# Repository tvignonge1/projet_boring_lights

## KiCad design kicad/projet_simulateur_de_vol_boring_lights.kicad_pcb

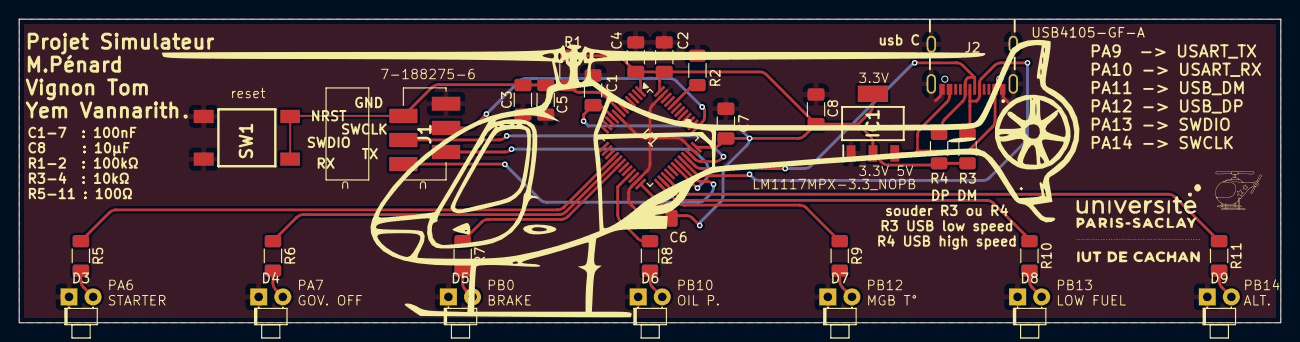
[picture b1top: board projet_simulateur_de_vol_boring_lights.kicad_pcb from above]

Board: 2 copper layers, 133.0 x 32.0 mm, 31 parts (0 on the bottom side), 25 nets.

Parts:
C1, C2, C3, C4, C5, C6, C7: 100n; C_1206_3216Metric_Pad1.33x1.80mm_HandSolder
C8: 10µ; C_1206_3216Metric_Pad1.33x1.80mm_HandSolder
D3: LED_starter; LED_D1.8mm_W1.8mm_H2.4mm_Horizontal_O1.27mm_Z1.6mm
D4: LED_gov.off; LED_D1.8mm_W1.8mm_H2.4mm_Horizontal_O1.27mm_Z1.6mm
D5: LED_brake; LED_D1.8mm_W1.8mm_H2.4mm_Horizontal_O1.27mm_Z1.6mm
D6: LED_oilP; LED_D1.8mm_W1.8mm_H2.4mm_Horizontal_O1.27mm_Z1.6mm
D7: LED_MGB T; LED_D1.8mm_W1.8mm_H2.4mm_Horizontal_O1.27mm_Z1.6mm
D8: LED_Low fuel; LED_D1.8mm_W1.8mm_H2.4mm_Horizontal_O1.27mm_Z1.6mm
D9: LED_Alt; LED_D1.8mm_W1.8mm_H2.4mm_Horizontal_O1.27mm_Z1.6mm
IC1: LM1117MPX-3.3_NOPB; SOT230P700X180-4N
J1: 7-188275-6; 71882756
J2: USB4105-GF-A; GCT_USB4105-GF-A
R1, R2: 100k; R_1206_3216Metric_Pad1.30x1.75mm_HandSolder
R3, R4: 10k; R_1206_3216Metric_Pad1.30x1.75mm_HandSolder
R5, R6, R7, R8, R9, R10, R11: 90; R_1206_3216Metric_Pad1.30x1.75mm_HandSolder
SW1: SW_Push; FSM2J
U1: STM32L073CZTx; LQFP-48_7x7mm_P0.5mm

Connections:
+3.3V: C1.1, C2.1, C4.1, C6.1, C7.1, C8.1, IC1.2 (OUTPUT), IC1.4 (VOUT), R1.1, R3.1, R4.1, U1.1 (VLCD), U1.9 (VDDA), U1.24 (VDD), U1.36 (VDD_USB), U1.48 (VDD)
+5V: IC1.3 (INPUT), J2.A4_B9 (VBUS), J2.B4_A9 (VBUS)
/NRST: C3.2, C5.1, J1.5, R1.2, SW1.2, U1.7 (NRST)
/SWCLK: J1.4, U1.37 (PA14)
/SWDIO: J1.3, U1.34 (PA13)
/USART_RX: J1.1, U1.31 (PA10)
/USART_TX: J1.2, U1.30 (PA9)
/USB_DM: J2.A7 (DN1), J2.B7 (DN2), R3.2, U1.32 (PA11)
/USB_DP: J2.A6 (DP1), J2.B6 (DP2), R4.2, U1.33 (PA12)
GND: C1.2, C2.2, C3.1, C4.2, C5.2, C6.2, C7.2, C8.2, D3.1 (K), D4.1 (K), D5.1 (K), D6.1 (K), D7.1 (K), D8.1 (K), D9.1 (K), IC1.1 (ADJ/GND), J1.6, J2.A1_B12 (GND), J2.B1_A12 (GND), J2.SH1 (SHELL_GND), J2.SH2 (SHELL_GND), J2.SH3 (SHELL_GND), J2.SH4 (SHELL_GND), R2.1, SW1.1, U1.8 (VSSA), U1.23 (VSS), U1.35 (VSS), U1.47 (VSS)
unnamed: D3.2 (A), R5.2
unnamed: D4.2 (A), R6.2
unnamed: D5.2 (A), R7.2
unnamed: D6.2 (A), R8.2
unnamed: D7.2 (A), R9.2
unnamed: D8.2 (A), R10.2
unnamed: D9.2 (A), R11.2
unnamed: R2.2, U1.44 (BOOT0)
unnamed: R5.1, U1.16 (PA6)
unnamed: R6.1, U1.17 (PA7)
unnamed: R7.1, U1.18 (PB0)
unnamed: R8.1, U1.21 (PB10)
unnamed: R9.1, U1.25 (PB12)
unnamed: R10.1, U1.26 (PB13)
unnamed: R11.1, U1.27 (PB14)

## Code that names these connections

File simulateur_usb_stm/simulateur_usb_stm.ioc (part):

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Mcu.Name=STM32L073C(B-Z)Tx
Mcu.Package=LQFP48
Mcu.UserName=STM32L073CZTx
PA11.Mode=Device
PA11.Signal=USB_DM
PA12.Mode=Device
PA12.Signal=USB_DP
PA13.Mode=Serial_Wire
PA13.Signal=SYS_SWDIO
PA14.Mode=Serial_Wire
PA14.Signal=SYS_SWCLK
PA2.Mode=Asynchronous
PA2.Signal=USART2_TX
PA3.Mode=Asynchronous
PA3.Signal=USART2_RX
PA6.GPIOParameters=GPIO_Label
PA6.GPIO_Label=Starter
PA6.Signal=GPIO_Output
PA7.GPIOParameters=GPIO_Label
PA7.GPIO_Label=GovOff
PA7.Signal=GPIO_Output
PB0.GPIOParameters=GPIO_Label
PB0.GPIO_Label=Brake
PB0.Signal=GPIO_Output
PB10.GPIOParameters=GPIO_Label
PB10.GPIO_Label=OilP
PB10.Signal=GPIO_Output
PB12.GPIOParameters=GPIO_Label
PB12.GPIO_Label=MGBT
PB12.Signal=GPIO_Output
PB13.GPIOParameters=GPIO_Label
PB13.GPIO_Label=LowFuel
PB13.Signal=GPIO_Output
PB14.GPIOParameters=GPIO_Label
PB14.GPIO_Label=Alt
PB14.Signal=GPIO_Output
RCC.HSE_VALUE=8000000
RCC.SYSCLKFreq_VALUE=16000000
RCC.SYSCLKSource=RCC_SYSCLKSOURCE_HSI
board=custom
